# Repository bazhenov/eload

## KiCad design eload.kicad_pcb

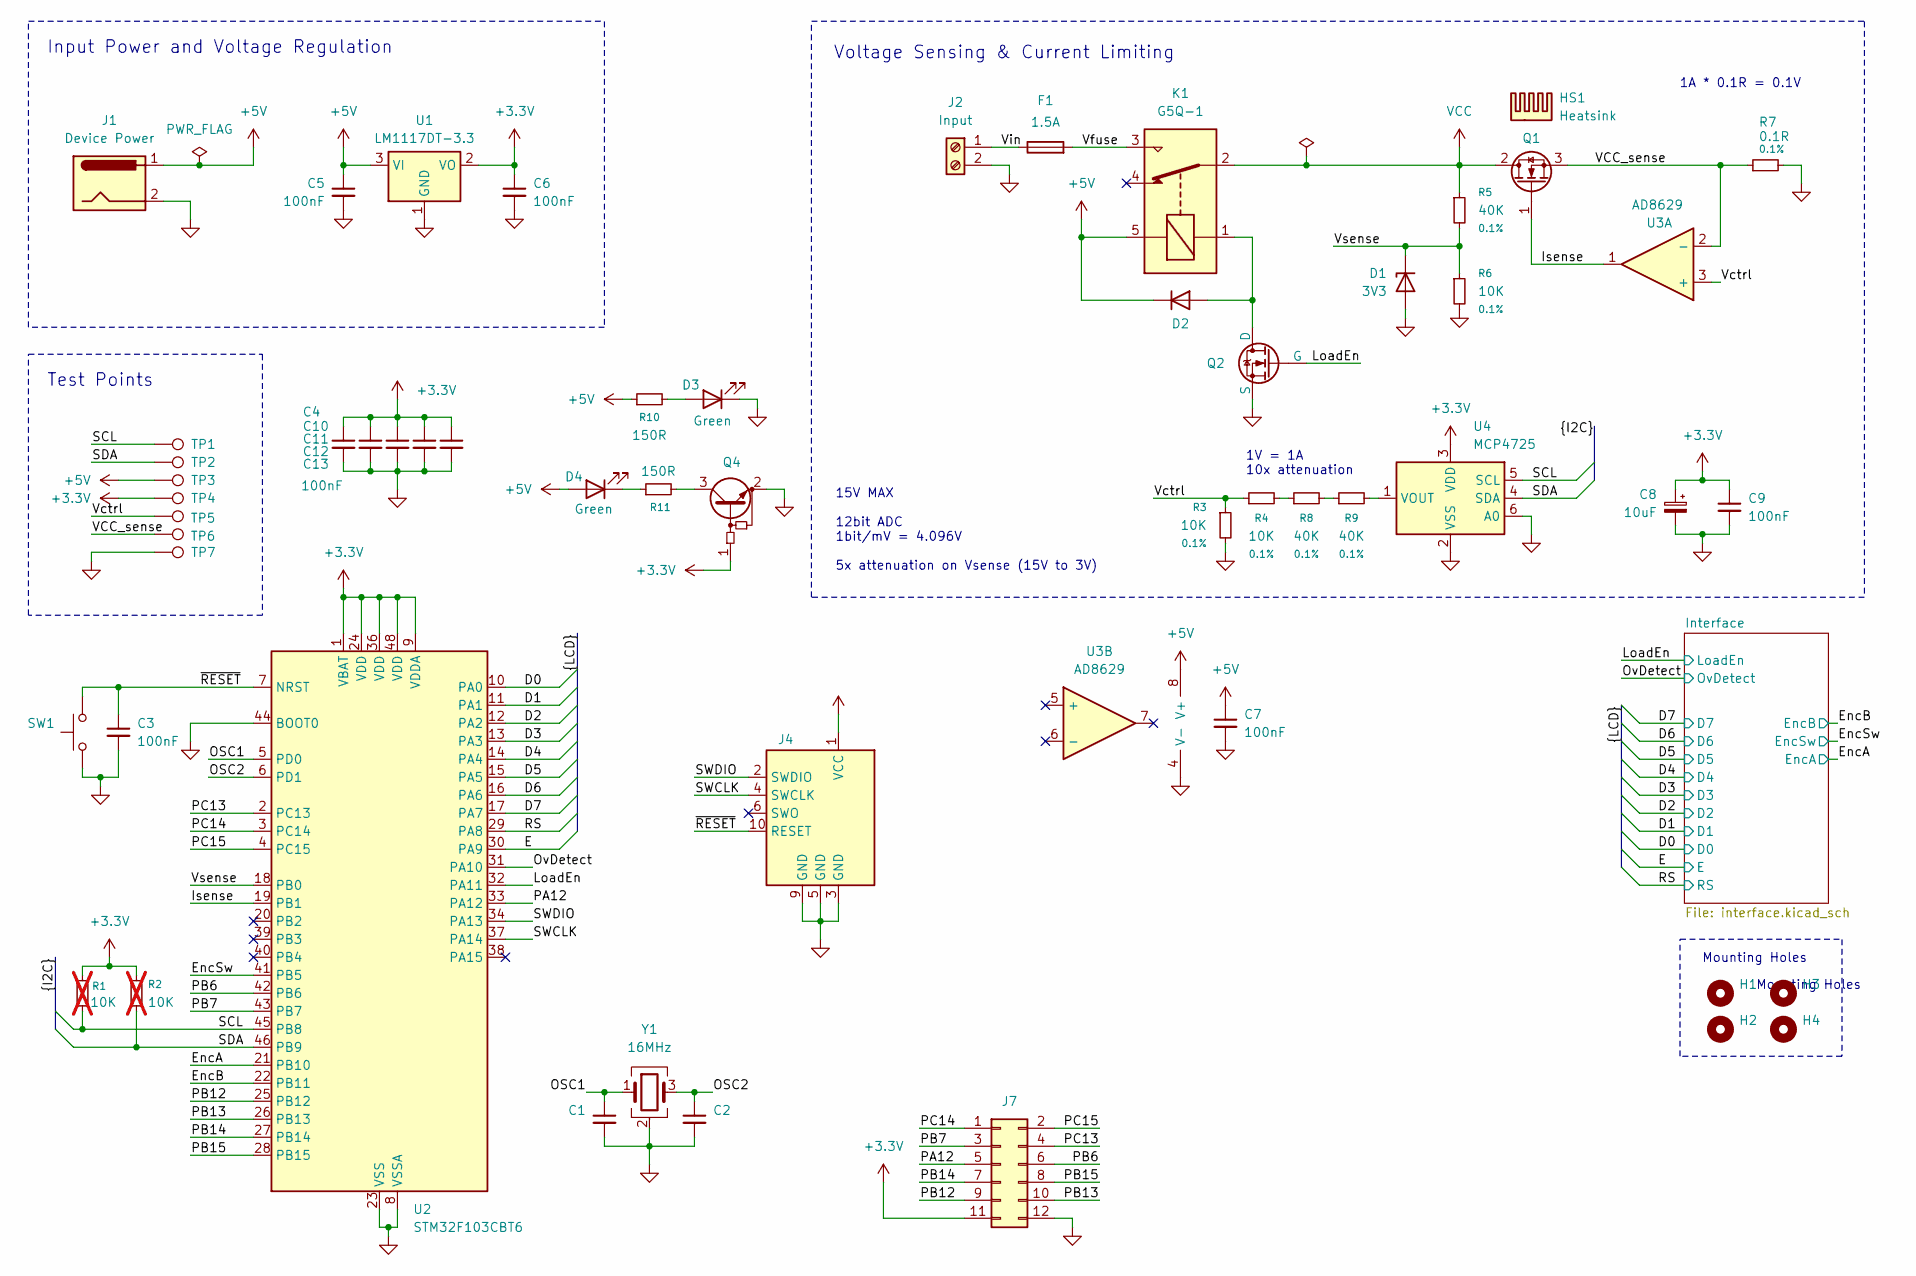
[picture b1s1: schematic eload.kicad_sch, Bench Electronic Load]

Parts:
C1, C2: 20pF; C_0805_2012Metric_Pad1.18x1.45mm_HandSolder; LCSC Part # C149606
C3, C4, C5, C6, C7, C9, C10, C11, C12, C13: 100nF; C_0805_2012Metric_Pad1.18x1.45mm_HandSolder; LCSC Part # C49678
C8: 10uF; CP_EIA-3216-18_Kemet-A_HandSolder; LCSC Part # C110055
D1: BZT52C3V3S; D_SOD-323_HandSoldering; LCSC Part # C507913
D2: MBR120VLSFT1G; D_SOD-123F; LCSC Part # C223608
D3, D4: 17-215/GHC-YR1S2/4T; LED_0805_2012Metric_Pad1.15x1.40mm_HandSolder; LCSC Part # C2985995
F1: 1.5A; R_Axial_DIN0204_L3.6mm_D1.6mm_P7.62mm_Horizontal; LCSC Part # C178932
H1, H2, H3, H4: MountingHole; MountingHole_3.2mm_M3_DIN965
HS1: Heatsink; XSD1226-362; LCSC Part # C4657
J1: Device Power; BarrelJack_Horizontal; LCSC Part # C7498153
J2: Input; TerminalBlock_CUI_TB007-508-02_1x02_P5.08mm_Horizontal; LCSC Part # C8465
J4: SWD Header; IDC-Header_2x05_P2.54mm_Vertical; LCSC Part # C5665
J7: Conn_02x06_Odd_Even; PinHeader_2x06_P2.54mm_Vertical
K1: G5Q-1; Relay_SPDT_Omron-G5Q-1; LCSC Part # C397241
Q1: RFP30N06LE-VB; TO-220-3_Vertical; LCSC Part # C878812
Q2: HL 40N05; SOT-23-3; LCSC Part # C7543825
Q4: DTC043ZUBTL; SOT-323_SC-70; LCSC Part # C962655
R1, R2: 10K; R_0805_2012Metric_Pad1.20x1.40mm_HandSolder; LCSC Part # C110775; not fitted
R3, R4, R6: 10K; R_0805_2012Metric_Pad1.20x1.40mm_HandSolder; LCSC Part # C110775
R5, R8, R9: 40K; R_0805_2012Metric_Pad1.20x1.40mm_HandSolder; LCSC Part # C865475
R7: 0.1R; R_1206_3216Metric_Pad1.30x1.75mm_HandSolder; LCSC Part # C7467250
R10, R11: 150R; R_0805_2012Metric_Pad1.20x1.40mm_HandSolder; LCSC Part # C844818
SW1: SW_Push
TP1, TP2, TP7: TestPoint; TestPoint_Loop_D1.80mm_Drill1.0mm_Beaded
TP3, TP4, TP5, TP6: TestPoint; TestPoint_Pad_D1.5mm
U1: LM1117DT-3.3; SOT-223; LCSC Part # C126027
U2: STM32F103CBT6; LQFP-48_7x7mm_P0.5mm; LCSC Part # C8304
U3: AD8629; JEITA_SOIC-8_3.9x4.9mm_P1.27mm; LCSC Part # C653045
U4: MCP4725; SOT-23-6; LCSC Part # C144198
Y1: 16MHz; Crystal_SMD_3225-4Pin_3.2x2.5mm_HandSoldering; LCSC Part # C13738

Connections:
+3.3V: C4.1, C6.1, C8.1, C9.1, C10.1, C11.1, C12.1, C13.1, J4.1 (VCC), J7.11, Q4.1 (B), R1.1, R2.1, TP4.1, U1.2 (VO), U2.1 (VBAT), U2.9 (VDDA), U2.24 (VDD), U2.36 (VDD), U2.48 (VDD), U4.3 (VDD); also elsewhere on the board
+5V: C5.1, C7.1, D2.1 (K), D4.2 (A), J1.1, K1.5, R10.1, TP3.1, U1.3 (VI), U3.8 (V+); also elsewhere on the board
/D0: U2.10 (PA0); also elsewhere on the board
/D1: U2.11 (PA1); also elsewhere on the board
/D2: U2.12 (PA2); also elsewhere on the board
/D3: U2.13 (PA3); also elsewhere on the board
/D4: U2.14 (PA4); also elsewhere on the board
/D5: U2.15 (PA5); also elsewhere on the board
/D6: U2.16 (PA6); also elsewhere on the board
/D7: U2.17 (PA7); also elsewhere on the board
/E: U2.30 (PA9); also elsewhere on the board
/EncA: U2.21 (PB10); also elsewhere on the board
/EncB: U2.22 (PB11); also elsewhere on the board
/EncSw: U2.41 (PB5); also elsewhere on the board
/Isense: Q1.1 (G), U2.19 (PB1), U3.1
/LoadEn: Q2.2 (G), U2.32 (PA11); also elsewhere on the board
/OSC1: C1.1, U2.5 (PD0), Y1.1
/OSC2: C2.1, U2.6 (PD1), Y1.3
/OvDetect: U2.31 (PA10); also elsewhere on the board
/PA12: J7.5, U2.33 (PA12)
/PB6: J7.6, U2.42 (PB6)
/PB7: J7.3, U2.43 (PB7)
/PB12: J7.9, U2.25 (PB12)
/PB13: J7.10, U2.26 (PB13)
/PB14: J7.7, U2.27 (PB14)
/PB15: J7.8, U2.28 (PB15)
/PC13: J7.4, U2.2 (PC13)
/PC14: J7.1, U2.3 (PC14)
/PC15: J7.2, U2.4 (PC15)
/RS: U2.29 (PA8); also elsewhere on the board
/SCL: R1.2, TP1.1, U2.45 (PB8), U4.5 (SCL)
/SDA: R2.2, TP2.1, U2.46 (PB9), U4.4 (SDA)
/SWCLK: J4.4 (SWCLK), U2.37 (PA14)
/SWDIO: J4.2 (SWDIO), U2.34 (PA13)
/VCC_sense: Q1.3 (S), R7.1, TP6.1, U3.2 (-)
/Vctrl: R3.1, R4.1, TP5.1, U3.3 (+)
/Vfuse: F1.2, K1.3
/Vin: F1.1, J2.1
/Vsense: D1.1 (K), R5.2, R6.1, U2.18 (PB0)
/~RESET: C3.1, J4.10 (RESET), SW1.2, U2.7 (NRST)
GND: C1.2, C2.2, C3.2, C4.2, C5.2, C6.2, C7.2, C8.2, C9.2, C10.2, C11.2, C12.2, C13.2, D1.2 (A), D3.1 (K), J1.2, J2.2, J4.3 (GND), J4.5 (GND), J4.9 (GND), J7.12, Q2.3 (S), Q4.2 (E), R3.2, R6.2, R7.2, SW1.1, TP7.1, U1.1 (GND), U2.8 (VSSA), U2.23 (VSS), U2.35 (VSS), U2.44 (BOOT0), U2.47 (VSS), U3.4 (V-), U4.2 (VSS), U4.6 (A0), Y1.2 (G), Y1.4 (G); also elsewhere on the board
unnamed: D2.2 (A), K1.1, Q2.1 (D)
unnamed: D3.2 (A), R10.2
unnamed: D4.1 (K), R11.1
unnamed: Q4.3 (C), R11.2
unnamed: R4.2, R8.1
unnamed: R8.2, R9.1
unnamed: R9.2, U4.1 (VOUT)
VCC: K1.2, Q1.2 (D), R5.1

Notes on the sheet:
Test Points
Voltage Sensing & Current Limiting
Input Power and Voltage Regulation
15V MAX 12bit ADC 1bit/mV = 4.096V 5x attenuation on Vsense (15V to 3V)
1A * 0.1R = 0.1V
1V = 1A 10x attenuation
Mounting Holes

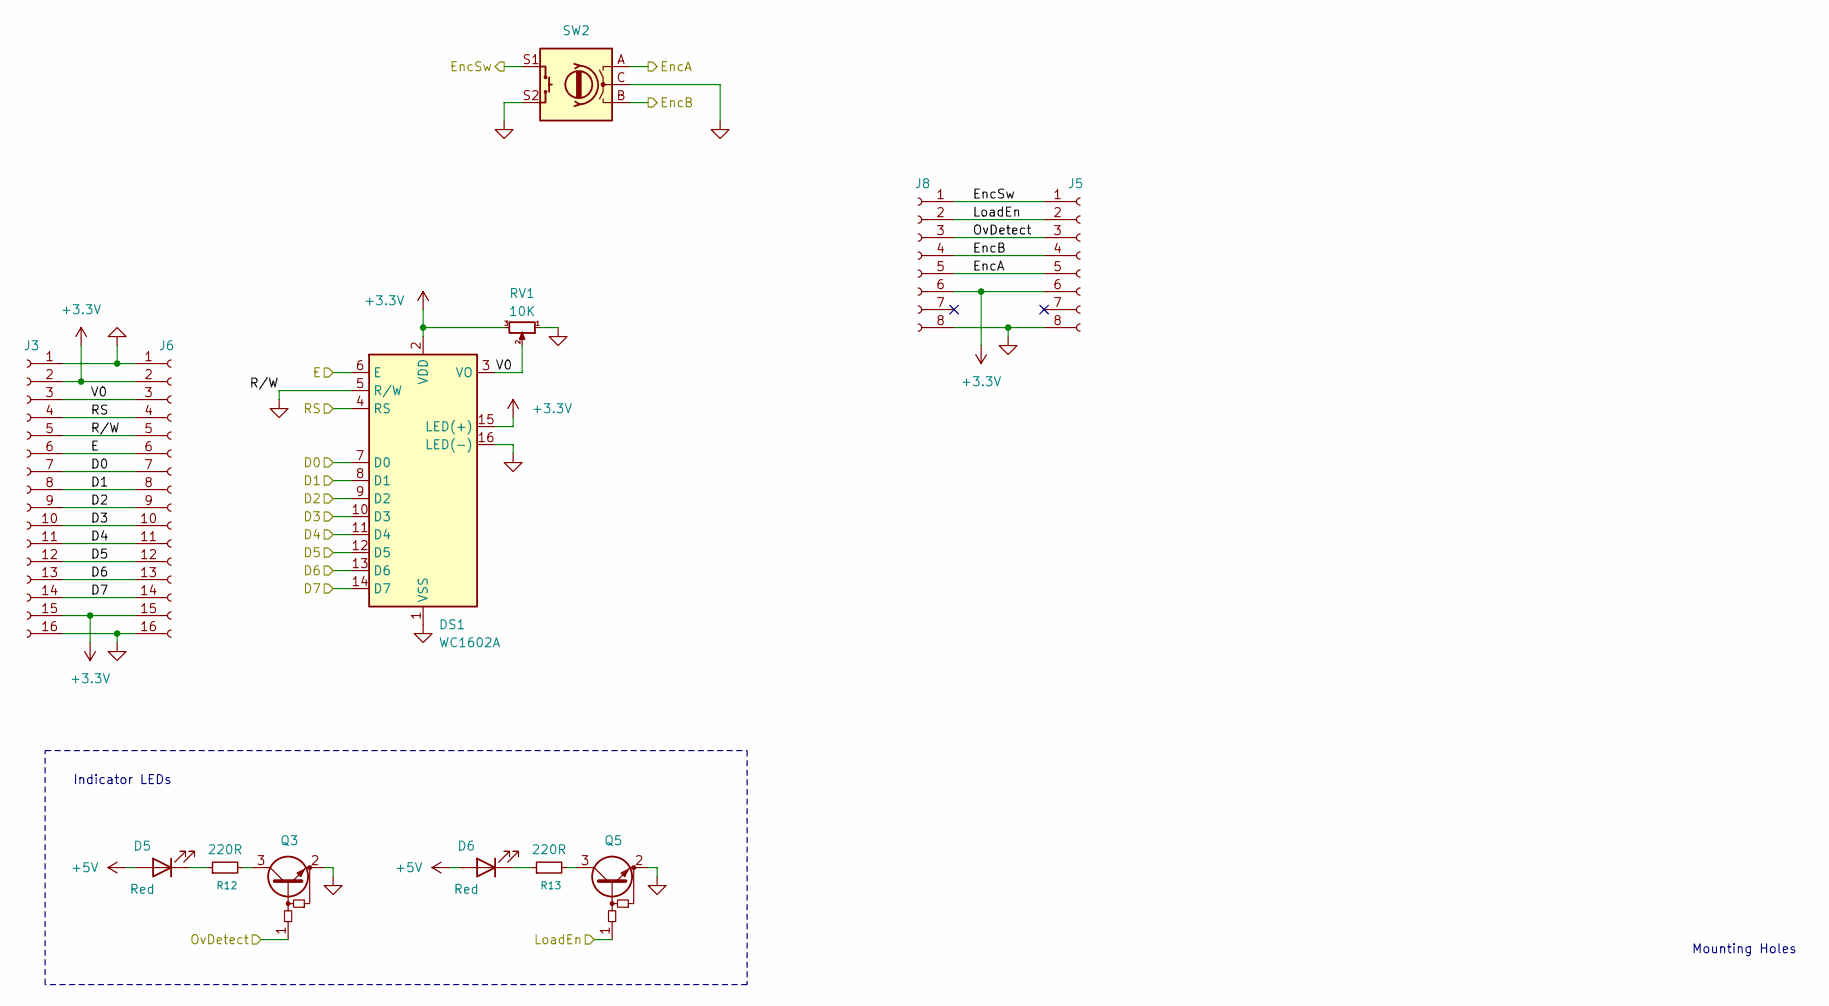
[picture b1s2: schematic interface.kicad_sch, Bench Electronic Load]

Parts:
D5, D6: 17-215/GHC-YR1S2/4T; LED_0805_2012Metric_Pad1.15x1.40mm_HandSolder; LCSC Part # C2971979
DS1: WC1602A
J3, J6: JST Header; JST_XH_B16B-XH-A_1x16_P2.50mm_Vertical; LCSC Part # C158022
J5, J8: Conn_01x08_Socket; JST_XH_B8B-XH-A_1x08_P2.50mm_Vertical
Q3, Q5: DTC043ZUBTL; SOT-323_SC-70; LCSC Part # C962655
R12, R13: 220R; R_0805_2012Metric_Pad1.20x1.40mm_HandSolder; LCSC Part # C844830
RV1: 10K; Potentiometer_Bourns_3266W_Vertical; LCSC Part # C49241482
SW2: RotaryEncoder_Switch; RotaryEncoder_Bourns_Vertical_PEC12R-3x17F-Sxxxx; LCSC Part # C5331618

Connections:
+3.3V: DS1.2 (VDD), DS1.15 (LED(+)), J3.2, J3.15, J5.6, J6.2, J6.15, J8.6, RV1.3; also elsewhere on the board
+5V: D5.2 (A), D6.2 (A); also elsewhere on the board
/D0: J3.7, J6.7; also elsewhere on the board
/D1: J3.8, J6.8; also elsewhere on the board
/D2: J3.9, J6.9; also elsewhere on the board
/D3: J3.10, J6.10; also elsewhere on the board
/D4: J3.11, J6.11; also elsewhere on the board
/D5: J3.12, J6.12; also elsewhere on the board
/D6: J3.13, J6.13; also elsewhere on the board
/D7: J3.14, J6.14; also elsewhere on the board
/E: J3.6, J6.6; also elsewhere on the board
/EncA: J5.5, J8.5; also elsewhere on the board
/EncB: J5.4, J8.4; also elsewhere on the board
/EncSw: J5.1, J8.1; also elsewhere on the board
/Interface/V0: DS1.3 (VO), J3.3, J6.3, RV1.2
/LoadEn: J5.2, J8.2, Q5.1 (B); also elsewhere on the board
/OvDetect: J5.3, J8.3, Q3.1 (B); also elsewhere on the board
/RS: J3.4, J6.4; also elsewhere on the board
GND: DS1.1 (VSS), DS1.5 (R/W), DS1.16 (LED(-)), J3.1, J3.5, J3.16, J5.8, J6.1, J6.5, J6.16, J8.8, Q3.2 (E), Q5.2 (E), RV1.1, SW2.C, SW2.S2; also elsewhere on the board
unnamed: D5.1 (K), R12.1
unnamed: D6.1 (K), R13.1
unnamed: Q3.3 (C), R12.2
unnamed: Q5.3 (C), R13.2

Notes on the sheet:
Mounting Holes
Indicator LEDs

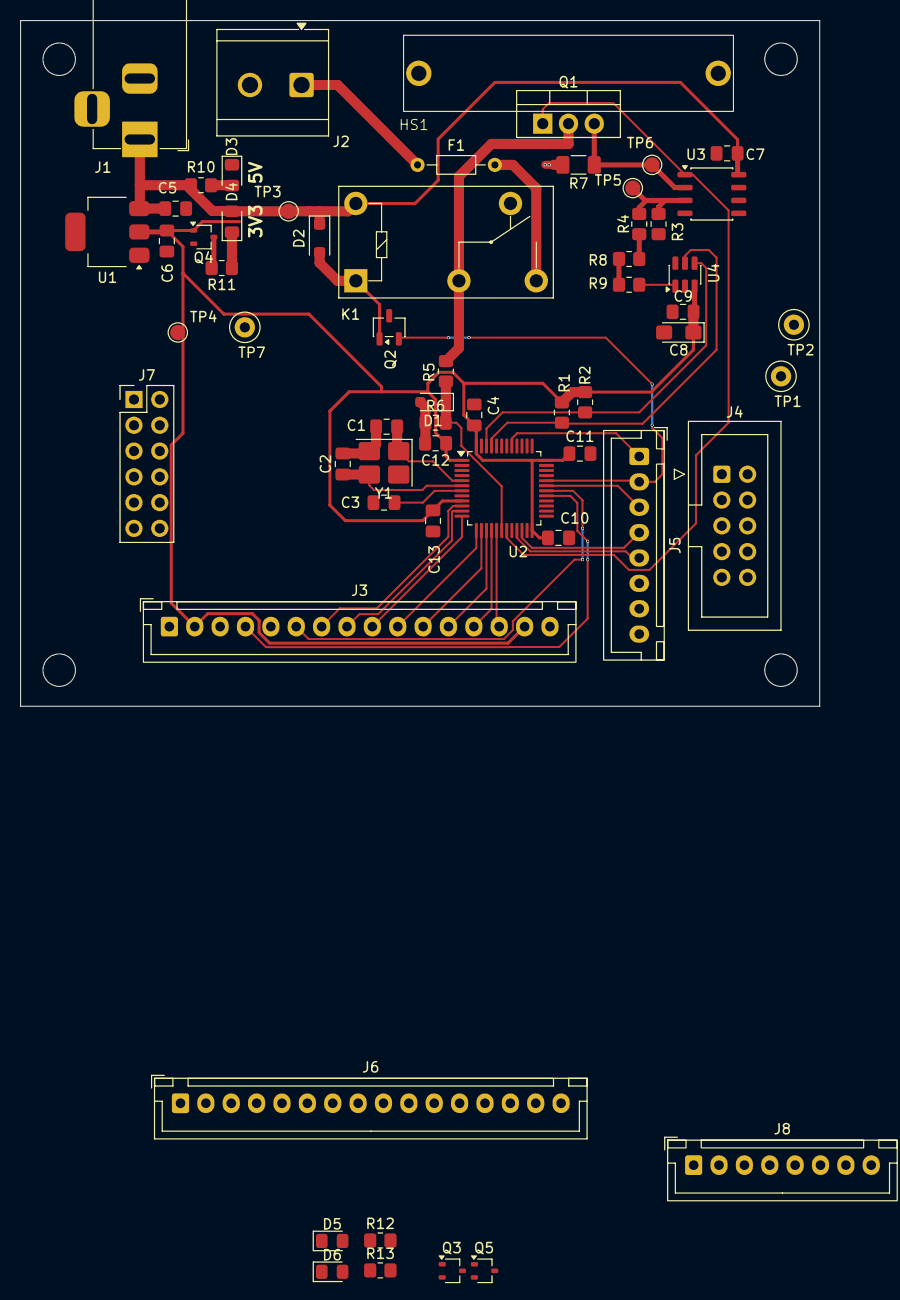
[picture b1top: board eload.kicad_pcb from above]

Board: 2 copper layers, 78.7 x 67.6 mm, 64 parts (0 on the bottom side), 54 nets.

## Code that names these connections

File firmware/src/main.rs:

//! Blinks an LED
//!
//! This assumes that a LED is connected to pc13 as is the case on the blue pill board.
//!
//! Note: Without additional hardware, PC13 should not be used to drive an LED, see page 5.1.2 of
//! the reference manual for an explanation. This is not an issue on the blue pill.

#![deny(unsafe_code)]
#![no_std]
#![no_main]

use core::{fmt::Write as _, mem};
use cortex_m_rt::entry;
use eload::{Encoder, EncoderValue, Led, LongPressButton, LongPressButtonValue};
use hd44780_driver::{
    HD44780,
    bus::{EightBitBus, EightBitBusPins},
    charset::{CharsetUniversal, Fallback},
    memory_map::{MemoryMap1602, StandardMemoryMap},
    setup::DisplayOptions8Bit,
};
use heapless::String;
use nb::block;
use panic_rtt_target as _;
use rtt_target::rtt_init_default;
use stm32f1xx_hal::{
    gpio::{Output, Pin},
    pac::{self, TIM1},
    prelude::*,
    timer::{DelayUs, Timer},
};

const CONTROL_RATE_HZ: u32 = 1000;
type EncoderLed<T> = Led<true, CONTROL_RATE_HZ, T>;
type EncoderButton<T> = LongPressButton<CONTROL_RATE_HZ, T>;

#[entry]
fn main() -> ! {
    let channels = rtt_init_default!();
    rtt_target::set_print_channel(channels.up.0);

    // Get access to the core peripherals from the cortex-m crate
    let cp = cortex_m::Peripherals::take().unwrap();
    // Get access to the device specific peripherals from the peripheral access crate
    let dp = pac::Peripherals::take().unwrap();

    let mut rcc = dp.RCC.constrain();

    // Acquire the GPIOC peripheral
    let mut gpioa = dp.GPIOA.split(&mut rcc);
    let mut gpioc = dp.GPIOC.split(&mut rcc);
    let mut gpiob = dp.GPIOB.split(&mut rcc);

    // Write to an LCD
    // {
    let mut delay = dp.TIM1.delay_us(&mut rcc);

    let rs = gpioa.pa8.into_push_pull_output(&mut gpioa.crh);
    let en = gpioa.pa9.into_push_pull_output(&mut gpioa.crh);

    let d0 = gpioa.pa0.into_push_pull_output(&mut gpioa.crl);
    let d1 = gpioa.pa1.into_push_pull_output(&mut gpioa.crl);
    let d2 = gpioa.pa2.into_push_pull_output(&mut gpioa.crl);
    let d3 = gpioa.pa3.into_push_pull_output(&mut gpioa.crl);
    let d4 = gpioa.pa4.into_push_pull_output(&mut gpioa.crl);
    let d5 = gpioa.pa5.into_push_pull_output(&mut gpioa.crl);
    let d6 = gpioa.pa6.into_push_pull_output(&mut gpioa.crl);
    let d7 = gpioa.pa7.into_push_pull_output(&mut gpioa.crl);

    let mut lcd = HD44780::new(
        DisplayOptions8Bit::new(MemoryMap1602::new()).with_pins(EightBitBusPins {
            rs,
            en,
            d0,
            d1,
            d2,
            d3,
            d4,
            d5,
            d6,
            d7,
        }),
        &mut delay,
    )
    .ok()
    .unwrap();

    lcd.reset(&mut delay).unwrap();
    lcd.clear(&mut delay).unwrap();

    let mut lcd = Ui { lcd, delay };

    let pb5 = gpiob.pb5.into_pull_up_input(&mut gpiob.crl);
    let pb10 = gpiob.pb10.into_pull_up_input(&mut gpiob.crh);
    let pb11 = gpiob.pb11.into_pull_up_input(&mut gpiob.crh);
    let mut encoder = Encoder::new(pb10, pb11);
    let mut encoder_button = EncoderButton::new(pb5);

    let led_pin = gpioc.pc13.into_push_pull_output(&mut gpioc.crh);
    let mut led = EncoderLed::new(led_pin);

    // Configure the syst timer to trigger an update every second
    let mut timer = Timer::syst(cp.SYST, &rcc.clocks).counter_hz();
    timer.start(CONTROL_RATE_HZ.Hz()).unwrap();

    let mut state = State::default();

    let mut current_screen = Screens::Main(MainScreen);
    current_screen.draw(&mut lcd, &state);

    // Application event loop
    loop {
        // Scanning inputs
        let encoder_event = encoder.scan();
        let encoder_button_event = encoder_button.scan();

        let events = [
            encoder_event.map(InputEvent::Encoder),
            encoder_button_event.map(InputEvent::EncoderButton),
        ];

        // Updating app state beased on events
        for e in events.into_iter().flatten() {
            current_screen.handle_input(e, &mut state);
        }

        // Navigation between panels and updating UI
        if encoder_button_event == Some(LongPressButtonValue::LongPress) {
            current_screen = match current_screen {
                Screens::Main(_) => Screens::Ticks(TicksScreen::default()),
                Screens::Ticks(_) => Screens::Main(MainScreen),
            };
            current_screen.draw(&mut lcd, &state);
        } else {
            current_screen.update(&mut lcd, &state);
        }

        // Controlling external world
        if state.tick() {
            led.toggle();
        }

        block!(timer.wait()).unwrap();
    }
}

#[derive(PartialEq, Eq)]
enum InputEvent {
    Encoder(EncoderValue),
    EncoderButton(LongPressButtonValue),
}

pub struct State {
    ticks_max: u32,
    tick: u32,
}

impl Default for State {
    fn default() -> Self {
        Self {
            ticks_max: 20,
            tick: 0,
        }
    }
}

impl State {
    pub fn increase_freq(&mut self) {
        self.ticks_max = (self.ticks_max - 20).max(20);
    }

    pub fn decrease_freq(&mut self) {
        self.ticks_max = (self.ticks_max + 20).min(1000)
    }

    pub fn tick(&mut self) -> bool {
        if self.tick >= self.ticks_max {
            self.tick = 0;
            true
        } else {
            self.tick += 1;
            false
        }
    }
}

#[allow(clippy::type_complexity)]
struct Ui {
    lcd: HD44780<
        EightBitBus<
            Pin<'A', 8, Output>,
            Pin<'A', 9, Output>,
            Pin<'A', 0, Output>,
            Pin<'A', 1, Output>,
            Pin<'A', 2, Output>,
            Pin<'A', 3, Output>,
            Pin<'A', 4, Output>,
            Pin<'A', 5, Output>,
            Pin<'A', 6, Output>,
            Pin<'A', 7, Output>,
        >,
        StandardMemoryMap<16, 2>,
        Fallback<CharsetUniversal, 32>,
    >,
    delay: DelayUs<TIM1>,
}

enum Screens {
    Main(MainScreen),
    Ticks(TicksScreen),
}

impl Screen for Screens {
    type State = State;
    type Ui = Ui;
    type InputEvent = InputEvent;

    fn draw(&mut self, ui: &mut Ui, state: &State) {
        match self {
            Screens::Main(p) => p.draw(ui, state),
            Screens::Ticks(p) => p.draw(ui, state),
        }
    }

    fn handle_input(&mut self, inputs: InputEvent, state: &mut State) {
        match self {
            Screens::Main(p) => p.handle_input(inputs, state),
            Screens::Ticks(p) => p.handle_input(inputs, state),
        };
    }

    fn update(&mut self, ui: &mut Ui, state: &State) {
        match self {
            Screens::Main(p) => p.update(ui, state),
            Screens::Ticks(p) => p.update(ui, state),
        }
    }
}

trait Screen {
    type State;
    type Ui;
    type InputEvent;

    fn draw(&mut self, ui: &mut Self::Ui, state: &Self::State);
    fn handle_input(&mut self, _inputs: Self::InputEvent, _state: &mut Self::State) {}
    fn update(&mut self, _ui: &mut Ui, _state: &Self::State) {}
}

struct TicksScreen {
    redraw_ticks: bool,
}

impl Default for TicksScreen {
    fn default() -> Self {
        Self { redraw_ticks: true }
    }
}

impl Screen for TicksScreen {
    type State = State;
    type Ui = Ui;
    type InputEvent = InputEvent;

    fn handle_input(&mut self, ev: Self::InputEvent, state: &mut Self::State) {
        match ev {
            InputEvent::Encoder(EncoderValue::Cw) => {
                state.increase_freq();
                self.redraw_ticks = true;
            }
            InputEvent::Encoder(EncoderValue::Ccw) => {
                state.decrease_freq();
                self.redraw_ticks = true;
            }
            _ => {}
        }
    }

    fn draw(&mut self, ui: &mut Ui, state: &State) {
        ui.lcd.clear(&mut ui.delay).unwrap();
        ui.lcd.write_str("Ticks Panel", &mut ui.delay).unwrap();
        self.update(ui, state);
    }

    fn update(&mut self, ui: &mut Ui, state: &State) {
        if mem::take(&mut self.redraw_ticks) {
            let mut data = String::<4>::new();
            write!(&mut data, "{:4}", state.ticks_max).unwrap();
            let (cols, _) = ui.lcd.display_size().get();
            ui.lcd.set_cursor_xy((cols - 4, 0), &mut ui.delay).unwrap();
            ui.lcd.write_str(data.as_str(), &mut ui.delay).unwrap();
        }
    }
}

struct MainScreen;

impl Screen for MainScreen {
    type State = State;
    type Ui = Ui;
    type InputEvent = InputEvent;

    fn draw(&mut self, ui: &mut Self::Ui, _state: &Self::State) {
        ui.lcd.clear(&mut ui.delay).unwrap();
        ui.lcd.write_str("Main Panel", &mut ui.delay).unwrap();
    }
}

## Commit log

2025-11-24 Schematics updated
2025-11-25 Schematics - Power Rail
2025-11-25 gitignore datasheets folder added
2025-11-25 SPE simulatiobn added
2025-11-26 Schematics updated
    - fuse added
    - rotary encoder connected
    - LCD added
    - switches added
    - minor fixes
2025-11-26 Changes to schematics
2025-11-29 Working on ERC checks
2025-11-30 SWD header
2025-12-11 Firmware setup
2025-12-11 Changing encoder pins to PB10/11
2025-12-11 Encoder/Led experiment
2025-12-13 hd44780 driver added
2025-12-13 Remote unneded buttons for now
2025-12-13 LongPressButton implemented
2025-12-16 Panels UI
2025-12-16 Seems like it's working
2025-12-16 Working example
2025-12-19 Updating simulation files
2025-12-19 WIP schematic
2025-12-19 Update footprints
2025-12-21 Updates in a schematics
2025-12-21 Test workflow
2025-12-25 Simulation for a IRLML6344 MOSFET
2025-12-25 Move AD8629 power rail to 5V
2025-12-25 Routing power plane for STM32
2025-12-29 Banana connector
2025-12-29 Replace 89.8K resistor with 10+40+40K
2025-12-29 Input Relay added
    OMRON G5Q-1
2025-12-30 Indicator LEDs added, pin header symbol changed
2025-12-30 ERC fixes
2026-01-04 Putting SWD header in a project local library
2026-01-04 Updating .gitignore
2026-01-04 Disabling DRC, not ready yet
2026-01-04 Split schematics into 2 pages
2026-01-04 EMF supressing diode and relay MOSFET has been choosed
2026-01-04 Biased NPN transistor correct schematic symbol, Resistor values
2026-01-10 3D models added, mounting holes added
2026-01-11 Update heatsink model
2026-01-13 PCB routing and cleanup
2026-01-13 PCB routing
2026-01-16 Transistor updated to MOSFET
2026-01-16 Update digital transistor to more solderable by hand
2026-01-16 Trying updated kicad action
2026-01-16 version
2026-01-16 Update kicad version
2026-01-16 Update to KiCad 9.0.7 library
